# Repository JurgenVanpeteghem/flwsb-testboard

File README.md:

# flwsb-testboard

# FLWSB I/O testboard
This is a testboard designed to test all the I/O pins of the FLWSB main board. 
Input functionality of the pin can be tested with a push button with pull-down configuration. Output can be tested with an led.

# Schematic 

# PCB design

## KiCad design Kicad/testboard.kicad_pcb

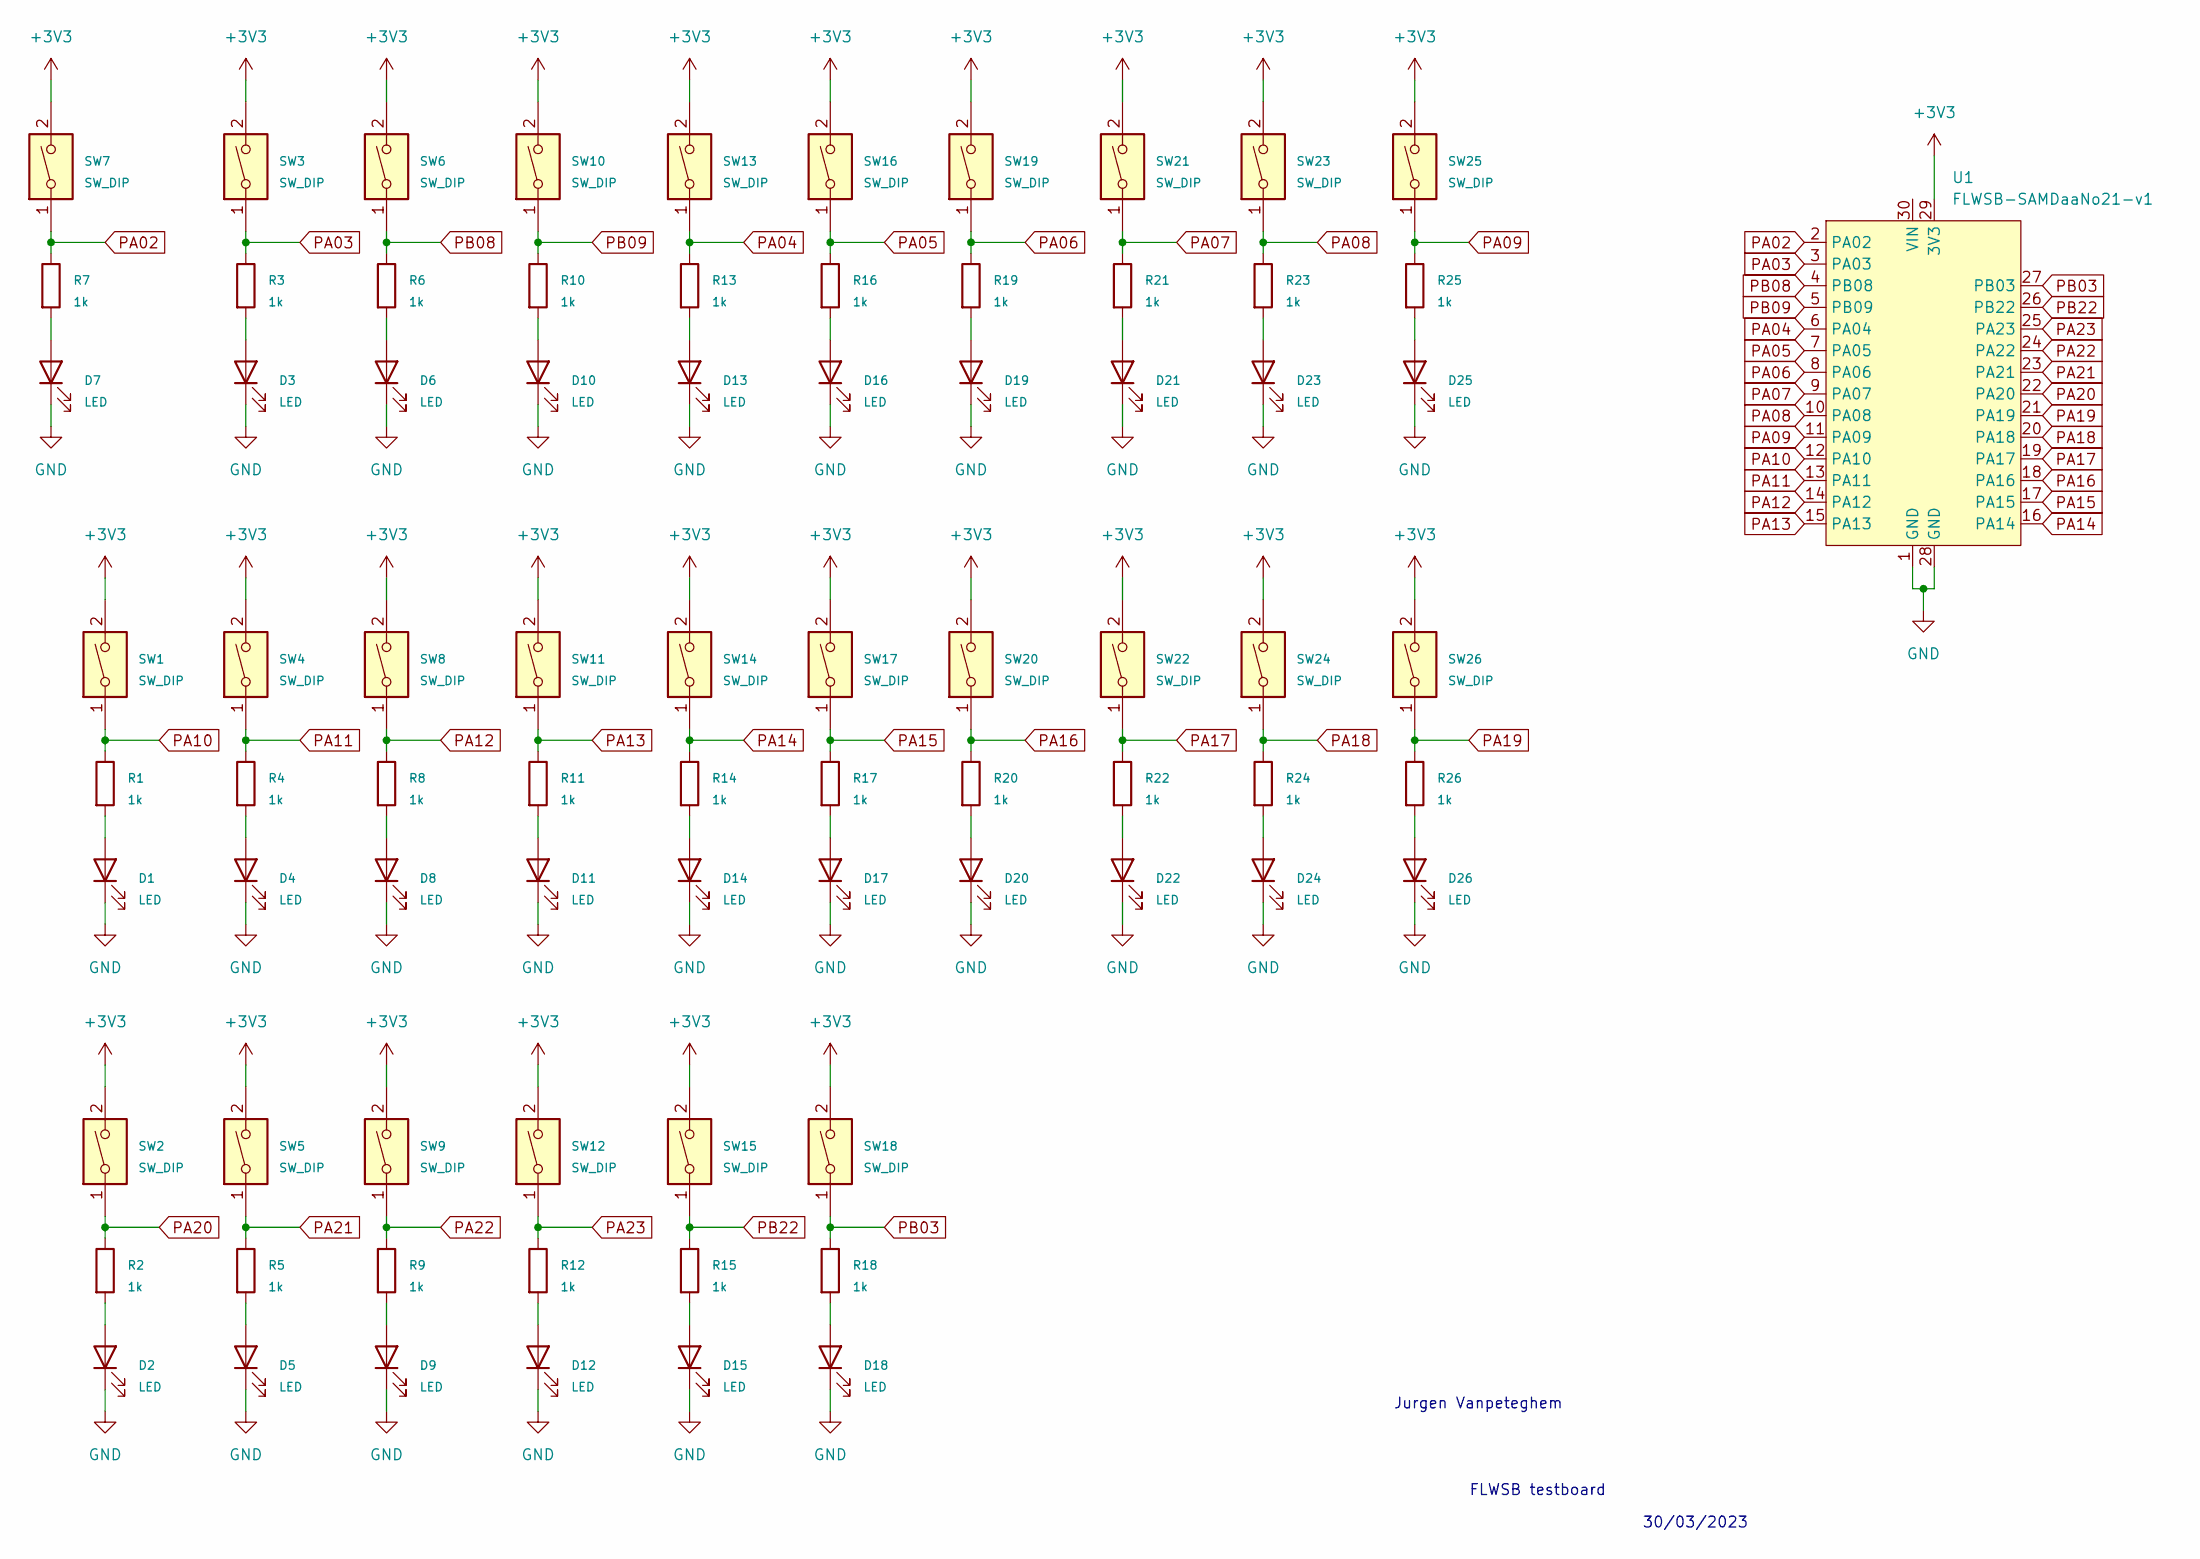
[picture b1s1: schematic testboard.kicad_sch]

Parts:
D1, D2, D3, D4, D5, D6, D7, D8, D9, D10, D11, D12, D13, D14, D15, D16, D17, D18, D19, D20, D21, D22, D23, D24, D25, D26: LED; LED_0805_2012Metric_Pad1.15x1.40mm_HandSolder
R1, R2, R3, R4, R5, R6, R7, R8, R9, R10, R11, R12, R13, R14, R15, R16, R17, R18, R19, R20, R21, R22, R23, R24, R25, R26: 1k; R_0805_2012Metric_Pad1.20x1.40mm_HandSolder
SW1, SW2, SW3, SW4, SW5, SW6, SW7, SW8, SW9, SW10, SW11, SW12, SW13, SW14, SW15, SW16, SW17, SW18, SW19, SW20, SW21, SW22, SW23, SW24, SW25, SW26: SW_DIP; SW_Push_1P1T_NO_6x6mm_H9.5mm
U1: FLWSB-SAMDaaNo21-v1

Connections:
+3V3: SW1.2, SW2.2, SW3.2, SW4.2, SW5.2, SW6.2, SW7.2, SW8.2, SW9.2, SW10.2, SW11.2, SW12.2, SW13.2, SW14.2, SW15.2, SW16.2, SW17.2, SW18.2, SW19.2, SW20.2, SW21.2, SW22.2, SW23.2, SW24.2, SW25.2, SW26.2, U1.29 (3V3)
GND: D1.1 (K), D2.1 (K), D3.1 (K), D4.1 (K), D5.1 (K), D6.1 (K), D7.1 (K), D8.1 (K), D9.1 (K), D10.1 (K), D11.1 (K), D12.1 (K), D13.1 (K), D14.1 (K), D15.1 (K), D16.1 (K), D17.1 (K), D18.1 (K), D19.1 (K), D20.1 (K), D21.1 (K), D22.1 (K), D23.1 (K), D24.1 (K), D25.1 (K), D26.1 (K), U1.1 (GND), U1.28 (GND)
unnamed: D1.2 (A), R1.2
unnamed: D2.2 (A), R2.2
unnamed: D3.2 (A), R3.2
unnamed: D4.2 (A), R4.2
unnamed: D5.2 (A), R5.2
unnamed: D6.2 (A), R6.2
unnamed: D7.2 (A), R7.2
unnamed: D8.2 (A), R8.2
unnamed: D9.2 (A), R9.2
unnamed: D10.2 (A), R10.2
unnamed: D11.2 (A), R11.2
unnamed: D12.2 (A), R12.2
unnamed: D13.2 (A), R13.2
unnamed: D14.2 (A), R14.2
unnamed: D15.2 (A), R15.2
unnamed: D16.2 (A), R16.2
unnamed: D17.2 (A), R17.2
unnamed: D18.2 (A), R18.2
unnamed: D19.2 (A), R19.2
unnamed: D20.2 (A), R20.2
unnamed: D21.2 (A), R21.2
unnamed: D22.2 (A), R22.2
unnamed: D23.2 (A), R23.2
unnamed: D24.2 (A), R24.2
unnamed: D25.2 (A), R25.2
unnamed: D26.2 (A), R26.2
PA02: R7.1, SW7.1, U1.2 (PA02)
PA03: R3.1, SW3.1, U1.3 (PA03)
PA04: R13.1, SW13.1, U1.6 (PA04)
PA05: R16.1, SW16.1, U1.7 (PA05)
PA06: R19.1, SW19.1, U1.8 (PA06)
PA07: R21.1, SW21.1, U1.9 (PA07)
PA08: R23.1, SW23.1, U1.10 (PA08)
PA09: R25.1, SW25.1, U1.11 (PA09)
PA10: R1.1, SW1.1, U1.12 (PA10)
PA11: R4.1, SW4.1, U1.13 (PA11)
PA12: R8.1, SW8.1, U1.14 (PA12)
PA13: R11.1, SW11.1, U1.15 (PA13)
PA14: R14.1, SW14.1, U1.16 (PA14)
PA15: R17.1, SW17.1, U1.17 (PA15)
PA16: R20.1, SW20.1, U1.18 (PA16)
PA17: R22.1, SW22.1, U1.19 (PA17)
PA18: R24.1, SW24.1, U1.20 (PA18)
PA19: R26.1, SW26.1, U1.21 (PA19)
PA20: R2.1, SW2.1, U1.22 (PA20)
PA21: R5.1, SW5.1, U1.23 (PA21)
PA22: R9.1, SW9.1, U1.24 (PA22)
PA23: R12.1, SW12.1, U1.25 (PA23)
PB03: R18.1, SW18.1, U1.27 (PB03)
PB08: R6.1, SW6.1, U1.4 (PB08)
PB09: R10.1, SW10.1, U1.5 (PB09)
PB22: R15.1, SW15.1, U1.26 (PB22)

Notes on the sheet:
30/03/2023
Jurgen Vanpeteghem
FLWSB testboard

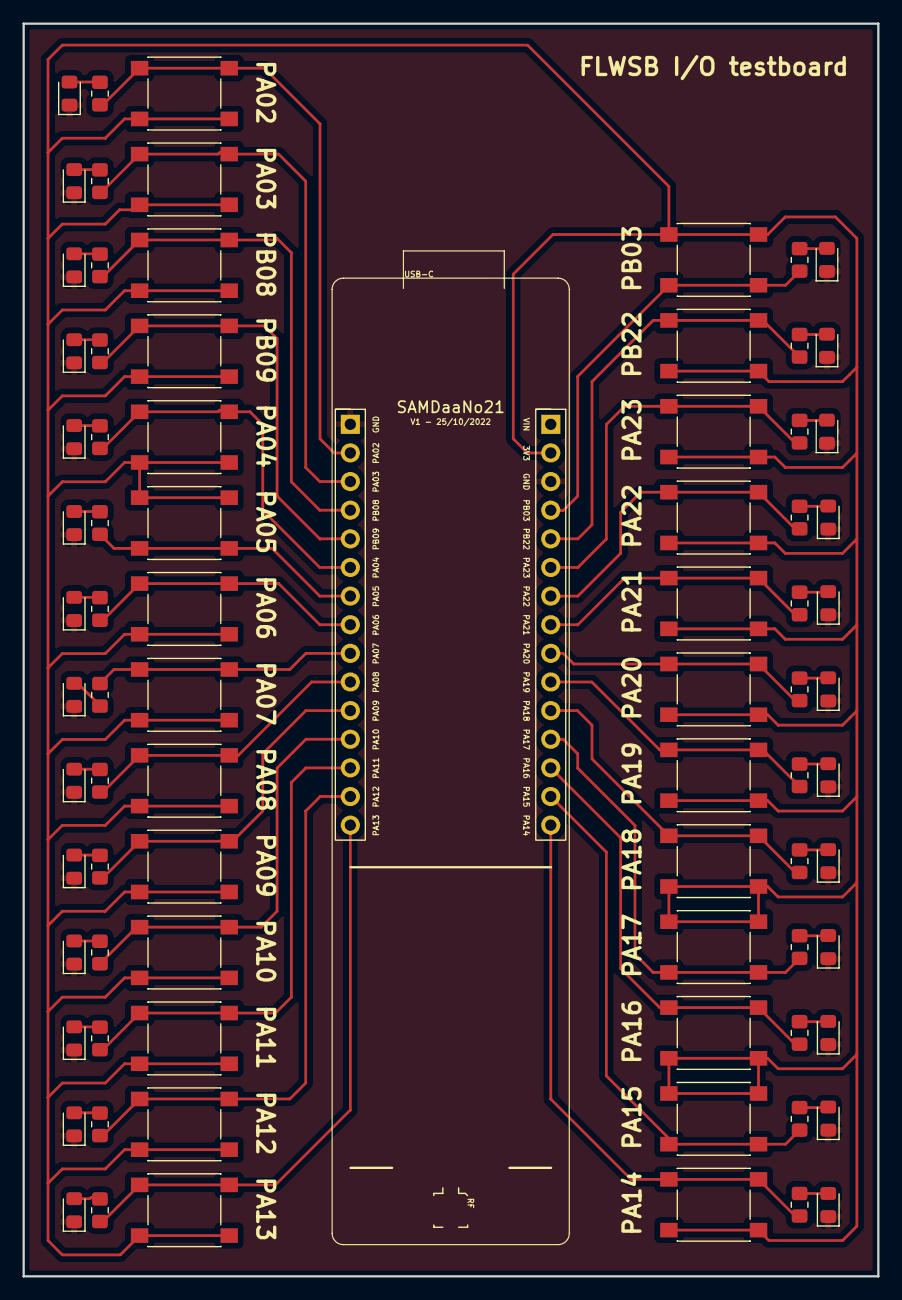
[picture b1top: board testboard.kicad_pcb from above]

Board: 2 copper layers, 75.8 x 111.1 mm, 79 parts (0 on the bottom side), 54 nets.

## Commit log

2023-06-06 Create testboard
2023-06-06 Kicad project files
